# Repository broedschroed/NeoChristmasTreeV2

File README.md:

# NeoChristmasTree V2

An ESP32-powered Christmas tree ornament built from two interlocking,
fir-tree-shaped PCBs, lit by 66 individually addressable WS2812 LEDs and
controlled by an IR remote or a browser-based pattern editor.

## Highlights

- **66x WS2812 LEDs** across 4 wings (2 PCBs plugged together at a right
  angle, front and back of each), plus 2 tip LEDs at the very top.
- **IR remote control** — direct pattern selection, brightness, on/off, and
  a learnable sleep timer (30 minutes to 4 hours, set by repeatedly pressing
  the Timer button; the tree shows the corresponding "level" of its wings as
  live feedback).
- **Remote-learning mode** — any compatible IR remote's 13 buttons can be
  taught to the tree, with LED feedback on the tree itself during learning.
- **Browser-based pattern editor** — while powered via USB, the tree opens
  a local WiFi access point with a web UI (served from LittleFS) to create,
  edit, preview, and transfer lighting patterns between two trees.
- **Automatic brightness** — an onboard light sensor (LDR) adjusts LED
  brightness to the ambient light, capped by the brightness set via remote.
- **Proper power management** — on battery, switching off fully cuts power
  via a FET-driven double-click of the physical power button; on USB, the
  regulator stays active and only the LEDs go dark.

## Hardware

- ESP32 (NeoPixel data on pin 16)
- VS1838B IR receiver
- LDR for ambient-light sensing
- FET power switch to emulate a double-click power-off on battery
- Two interlocking fir-tree-shaped PCBs ("Tannenfluegellaengs" and
  "Tannenfluegelquer"), each carrying 32 of the 66 LEDs
- Main control board ("TannenbasisV4") carrying the ESP32, IR receiver, LDR
  and power management; KiCad sources for all three boards under
  `docs/Leiterplatten/`
- 3D-printed base housing; STL files under `docs/Gehäuse/`

## Repository layout

- `*.ino` / `*.h` — firmware (Arduino/ESP32 sketch)
- `data/www/` — the pattern editor web UI, uploaded to the ESP32's LittleFS
  filesystem (Arduino IDE "ESP32 Sketch Data Upload" or equivalent)
- `docs/manual/` — user manual (PDF)
- `docs/system/` — system documentation (PDF; describes an earlier hardware
  revision, kept for reference)
- `docs/Leiterplatten/` — KiCad sources, gerbers, schematic and front/back
  PCB renders for the control board and the two wing PCBs
- `docs/Gehäuse/` — STL files for the 3D-printed base housing
- `docs/Bilder/` — photos and a short clip of the finished tree

## Building

Open `NeoChristmasTreeV2.ino` in the Arduino IDE (or arduino-cli) with the
ESP32 core installed, plus the libraries IRremote, Adafruit NeoPixel,
ArduinoJson, and ESPAsyncWebServer. Flash the sketch, then upload the
contents of `data/` to the ESP32's LittleFS filesystem (e.g. via the "ESP32
Sketch Data Upload" tool) to make the pattern editor available.

Hold the mode/learn switch while powering on to enter IR remote-learning
mode.

## License

Released under the [MIT License](LICENSE).

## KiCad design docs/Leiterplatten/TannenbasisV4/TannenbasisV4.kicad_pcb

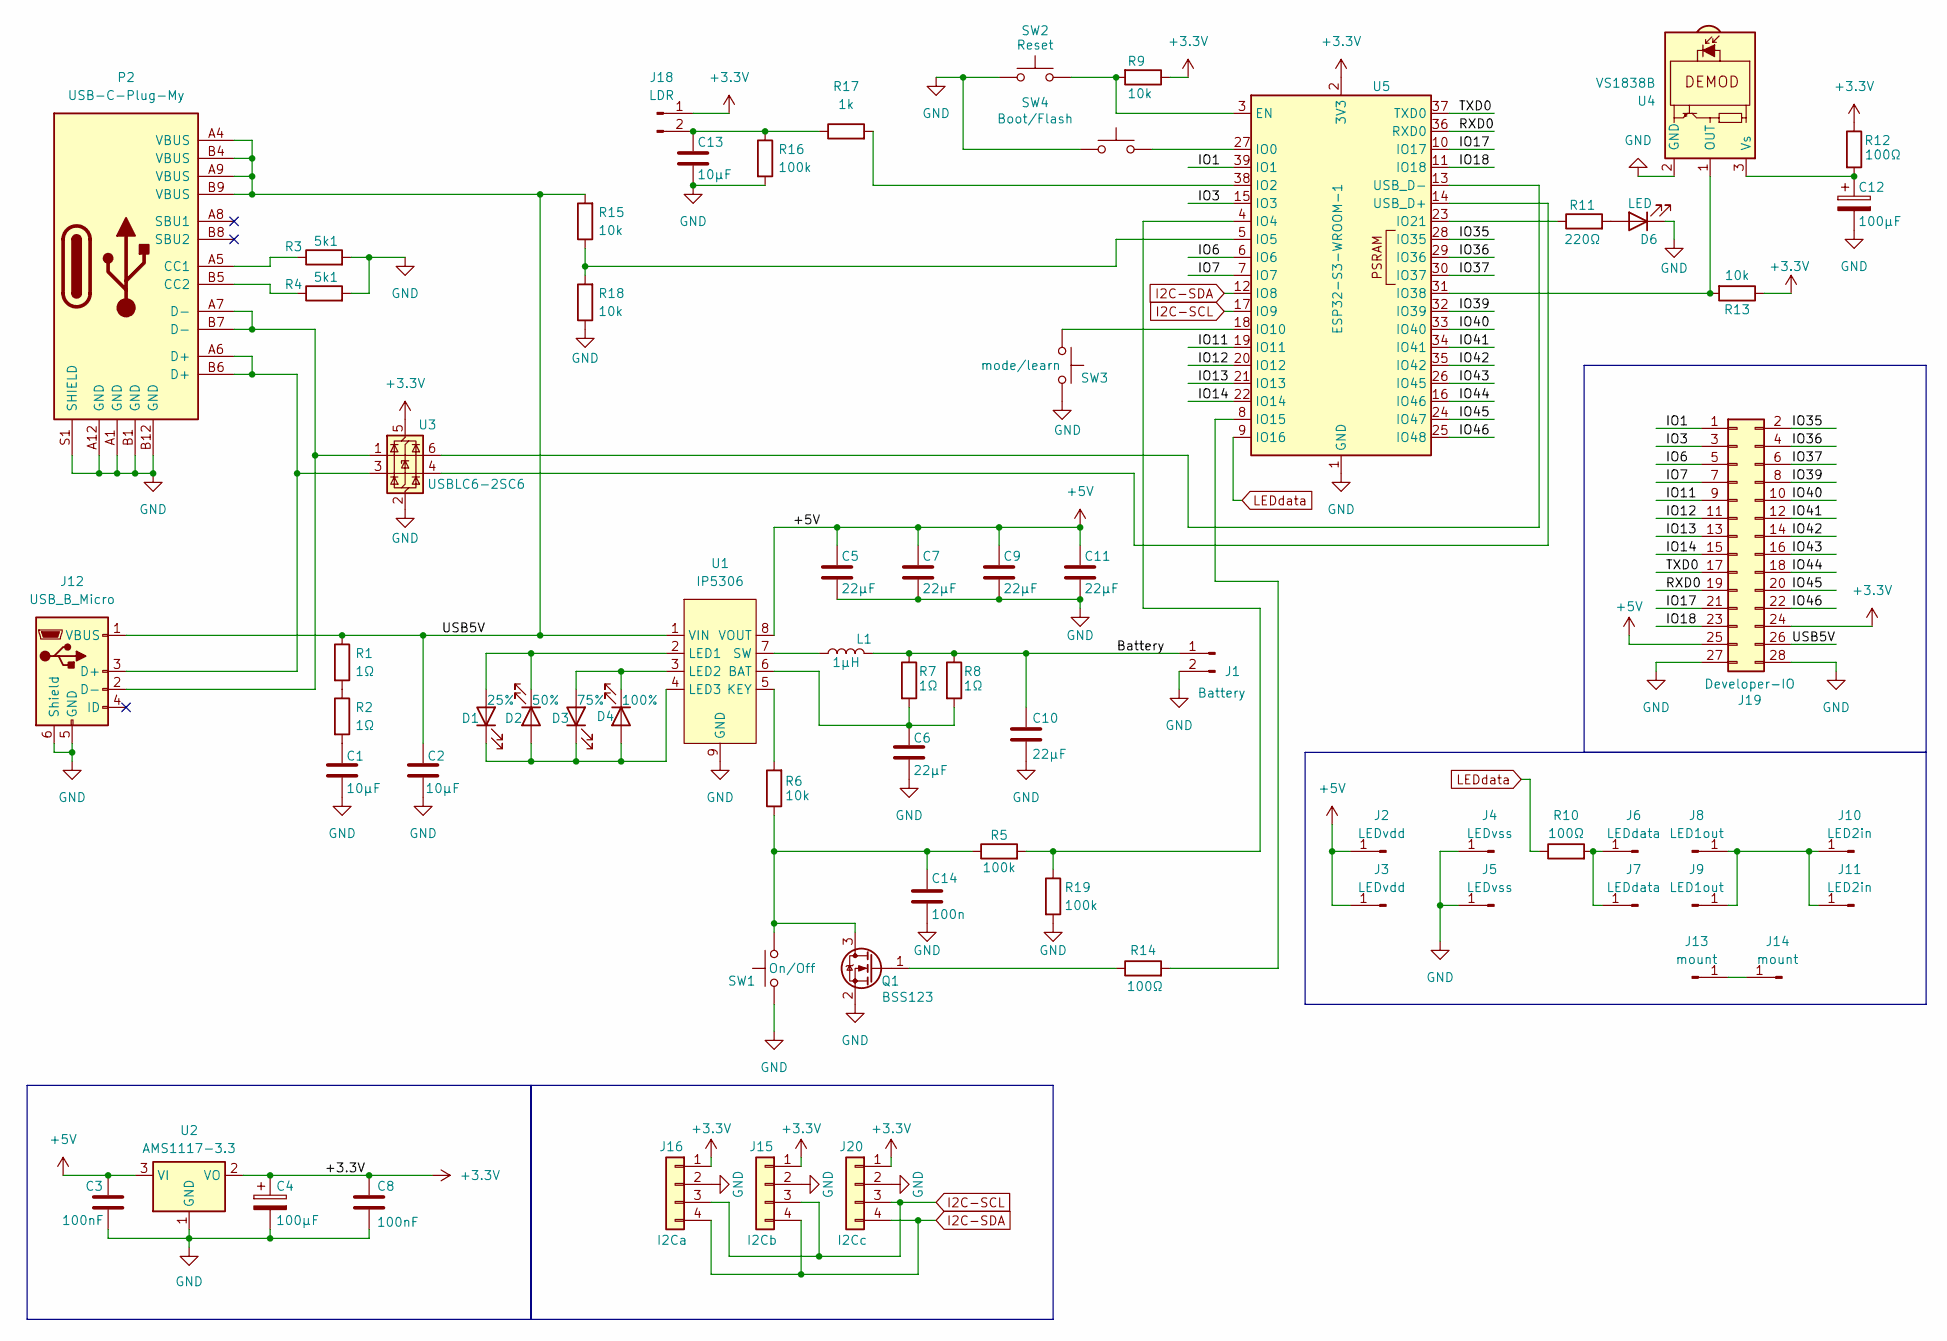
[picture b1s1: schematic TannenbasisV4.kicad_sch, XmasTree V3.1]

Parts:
C1, C2, C13: 10µF; C_0805_2012Metric_Pad1.18x1.45mm_HandSolder
C3, C8: 100nF; C_0805_2012Metric_Pad1.18x1.45mm_HandSolder
C4, C12: 100µF; CP_Radial_D6.3mm_P2.50mm
C5, C6, C7, C9, C10, C11: 22µF; C_1210_3225Metric_Pad1.33x2.70mm_HandSolder
C14: 100n; C_0805_2012Metric_Pad1.18x1.45mm_HandSolder
D1: 25%; LED_1210_3225Metric_Pad1.42x2.65mm_HandSolder
D2: 50%; LED_1210_3225Metric_Pad1.42x2.65mm_HandSolder
D3: 75%; LED_1210_3225Metric_Pad1.42x2.65mm_HandSolder
D4: 100%; LED_1210_3225Metric_Pad1.42x2.65mm_HandSolder
D6: LED; LED_1210_3225Metric_Pad1.42x2.65mm_HandSolder
J1: Battery; PinHeader_1x02_P2.54mm_Vertical
J2, J3: LEDvdd; solderconnect-1
J4, J5: LEDvss; solderconnect-1
J6, J7: LEDdata; solderconnect-1
J8, J9: LED1out; solderconnect-1
J10, J11: LED2in; solderconnect-1
J12: USB_B_Micro; USB_Micro-B_Pins
J13, J14: mount; solderconnect-1
J15: I2Cb; PinHeader_1x04_P2.54mm_Vertical
J16: I2Ca; PinHeader_1x04_P2.54mm_Vertical
J18: LDR; PinHeader_1x02_P2.54mm_Vertical
J19: Developer-IO; PinHeader_2x14_P2.54mm_Vertical
J20: I2Cc; PinHeader_1x04_P2.54mm_Vertical
L1: 1µH; MyPowerCoil
P2: USB-C-Plug-My; MyUSB-C
Q1: BSS123; SOT-23
R1, R2, R7, R8: 1Ω; R_0805_2012Metric_Pad1.20x1.40mm_HandSolder
R3, R4: 5k1; R_0805_2012Metric_Pad1.20x1.40mm_HandSolder
R5, R16, R19: 100k; R_0805_2012Metric_Pad1.20x1.40mm_HandSolder
R6, R9, R13, R15, R18: 10k; R_0805_2012Metric_Pad1.20x1.40mm_HandSolder
R10, R12, R14: 100Ω; R_0805_2012Metric_Pad1.20x1.40mm_HandSolder
R11: 220Ω; R_0805_2012Metric_Pad1.20x1.40mm_HandSolder
R17: 1k; R_0805_2012Metric_Pad1.20x1.40mm_HandSolder
SW1: On/Off; SW_DIP_SPSTx01_Slide_6.7x4.1mm_W8.61mm_P2.54mm_LowProfile
SW2: Reset; SW_DIP_SPSTx01_Slide_6.7x4.1mm_W8.61mm_P2.54mm_LowProfile
SW3: mode/learn; SW_DIP_SPSTx01_Slide_6.7x4.1mm_W8.61mm_P2.54mm_LowProfile
SW4: Boot/Flash; SW_DIP_SPSTx01_Slide_6.7x4.1mm_W8.61mm_P2.54mm_LowProfile
U1: IP5306
U2: AMS1117-3.3; SOT-223-3_TabPin2
U3: USBLC6-2SC6; SOT-23-6
U4: VS1838B; Vishay_MOLD-3Pin
U5: ESP32-S3-WROOM-1

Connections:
+3.3V: C4.1, C8.1, J15.1, J16.1, J18.1, J19.24, J20.1, R9.1, R12.1, R13.1, U2.2 (VO), U3.5 (VBUS), U5.2 (3V3)
+5V: C3.1, C5.1, C7.1, C9.1, C11.1, J2.1, J3.1, J19.25, U1.8 (VOUT), U2.3 (VI)
/Battery: C10.1, J1.1, L1.2, R7.1, R8.1
/IO1: J19.1, U5.39 (IO1)
/IO3: J19.3, U5.15 (IO3)
/IO6: J19.5, U5.6 (IO6)
/IO7: J19.7, U5.7 (IO7)
/IO11: J19.9, U5.19 (IO11)
/IO12: J19.11, U5.20 (IO12)
/IO13: J19.13, U5.21 (IO13)
/IO14: J19.15, U5.22 (IO14)
/IO17: J19.21, U5.10 (IO17)
/IO18: J19.23, U5.11 (IO18)
/IO35: J19.2, U5.28 (IO35)
/IO36: J19.4, U5.29 (IO36)
/IO37: J19.6, U5.30 (IO37)
/IO39: J19.8, U5.32 (IO39)
/IO40: J19.10, U5.33 (IO40)
/IO41: J19.12, U5.34 (IO41)
/IO42: J19.14, U5.35 (IO42)
/IO43: J19.16, U5.26 (IO45)
/IO44: J19.18, U5.16 (IO46)
/IO45: J19.20, U5.24 (IO47)
/IO46: J19.22, U5.25 (IO48)
/RXD0: J19.19, U5.36 (RXD0)
/TXD0: J19.17, U5.37 (TXD0)
/USB5V: C2.1, J12.1 (VBUS), J19.26, P2.A4 (VBUS), P2.A9 (VBUS), P2.B4 (VBUS), P2.B9 (VBUS), R1.1, R15.2, U1.1 (VIN)
GND: C1.2, C2.2, C3.2, C4.2, C5.2, C6.2, C7.2, C8.2, C9.2, C10.2, C11.2, C12.2, C13.2, C14.2, D6.1 (K), J1.2, J4.1, J5.1, J12.5 (GND), J12.6 (Shield), J15.2, J16.2, J19.27, J19.28, J20.2, P2.A1 (GND), P2.A12 (GND), P2.B1 (GND), P2.B12 (GND), P2.S1 (SHIELD), Q1.2 (S), R3.2, R4.2, R16.2, R18.1, R19.2, SW1.1, SW2.1, SW3.2, SW4.2, U1.9 (GND), U2.1 (GND), U3.2 (GND), U4.2 (GND), U5.1 (GND), U5.40 (GND), U5.41 (GND)
I2C-SCL: J15.3, J16.3, J20.3, U5.17 (IO9)
I2C-SDA: J15.4, J16.4, J20.4, U5.12 (IO8)
LEDdata: R10.1, U5.9 (IO16)
unnamed: C1.1, R2.2
unnamed: D1.2 (A), D2.1 (K), U1.2 (LED1)
unnamed: D1.1 (K), D2.2 (A), D3.1 (K), D4.2 (A), U1.4 (LED3)
unnamed: D3.2 (A), D4.1 (K), U1.3 (LED2)
unnamed: D6.2 (A), R11.2
unnamed: J6.1, J7.1, R10.2
unnamed: J8.1, J9.1, J10.1, J11.1
unnamed: J12.3 (D+), P2.A6 (D+), P2.B6 (D+), U3.3 (I/O2)
unnamed: J12.2 (D-), P2.A7 (D-), P2.B7 (D-), U3.1 (I/O1)
unnamed: J13.1, J14.1
unnamed: C13.1, J18.2, R16.1, R17.1
unnamed: P2.A5 (CC1), R3.1
unnamed: P2.B5 (CC2), R4.1
unnamed: C14.1, Q1.3 (D), R5.1, R6.1, SW1.2
unnamed: Q1.1 (G), R14.1
unnamed: R1.2, R2.1
unnamed: C6.1, R7.2, R8.2, U1.6 (BAT)
unnamed: R6.2, U1.5 (KEY)
unnamed: L1.1, U1.7 (SW)
unnamed: R13.2, U4.1 (OUT), U5.31 (IO38)
unnamed: C12.1, R12.2, U4.3 (Vs)
unnamed: R9.2, SW2.2, U5.3 (EN)
unnamed: SW4.1, U5.27 (IO0)
unnamed: R17.2, U5.38 (IO2)
unnamed: R5.2, R19.1, U5.4 (IO4)
unnamed: R15.1, R18.2, U5.5 (IO5)
unnamed: SW3.1, U5.18 (IO10)
unnamed: R14.2, U5.8 (IO15)
unnamed: R11.1, U5.23 (IO21)
unnamed: U3.4 (I/O2), U5.14 (USB_D+)
unnamed: U3.6 (I/O1), U5.13 (USB_D-)

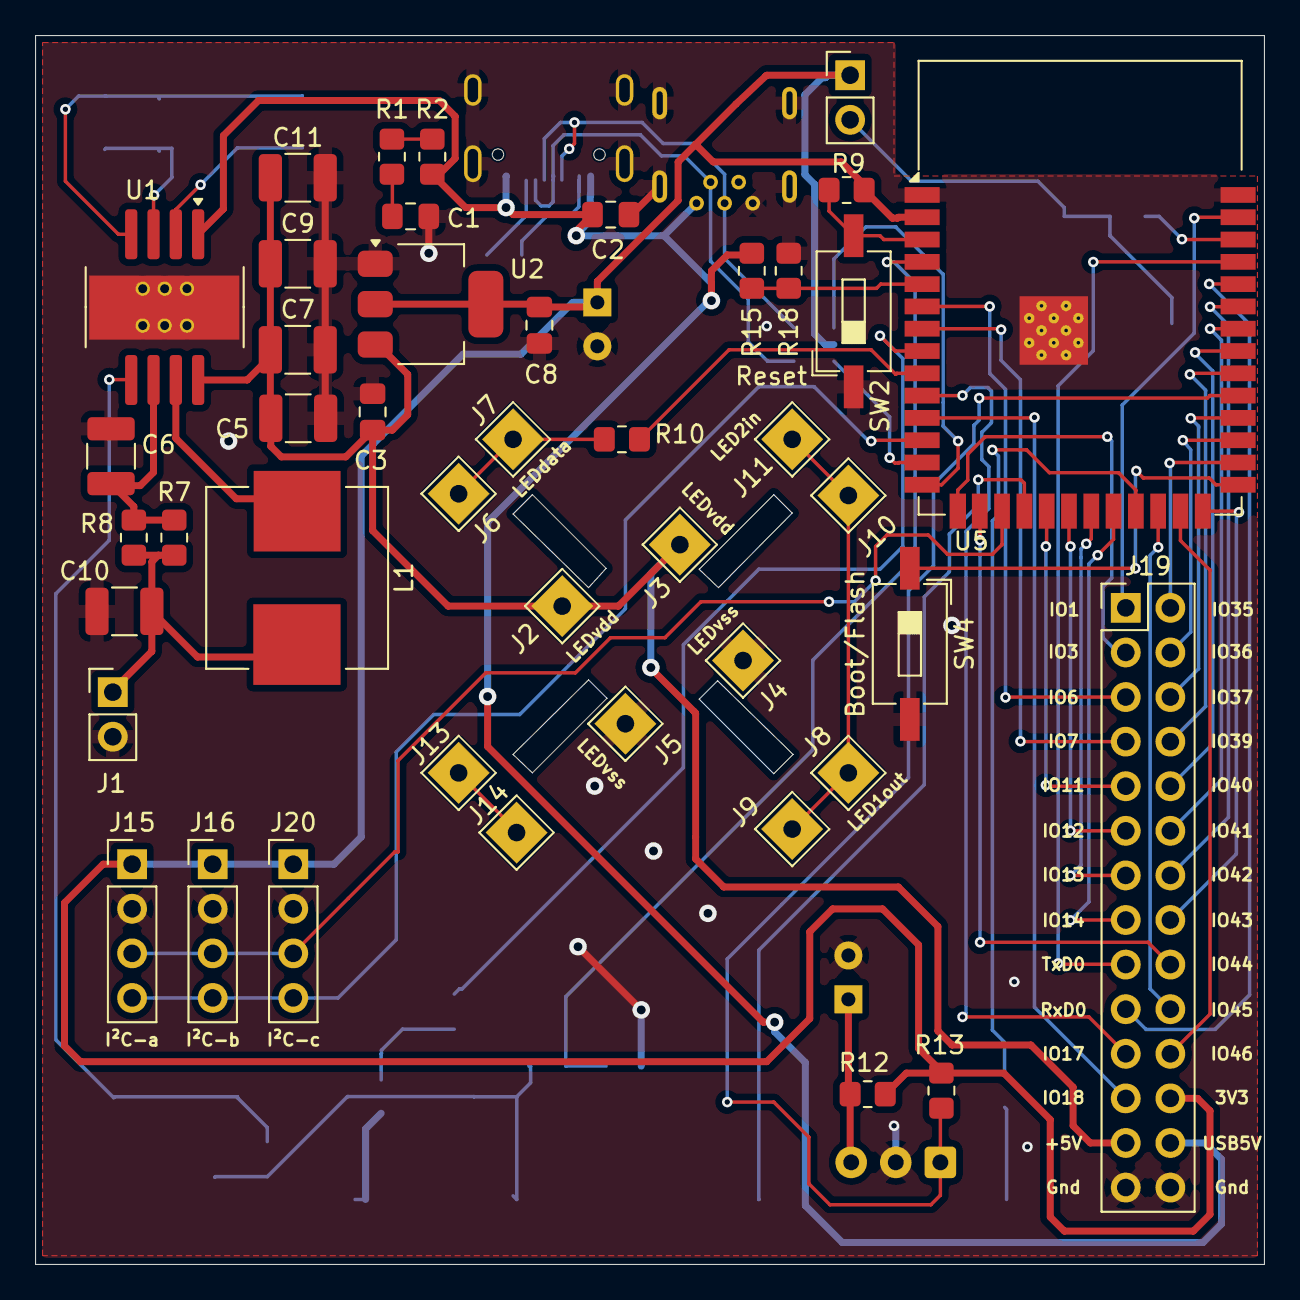
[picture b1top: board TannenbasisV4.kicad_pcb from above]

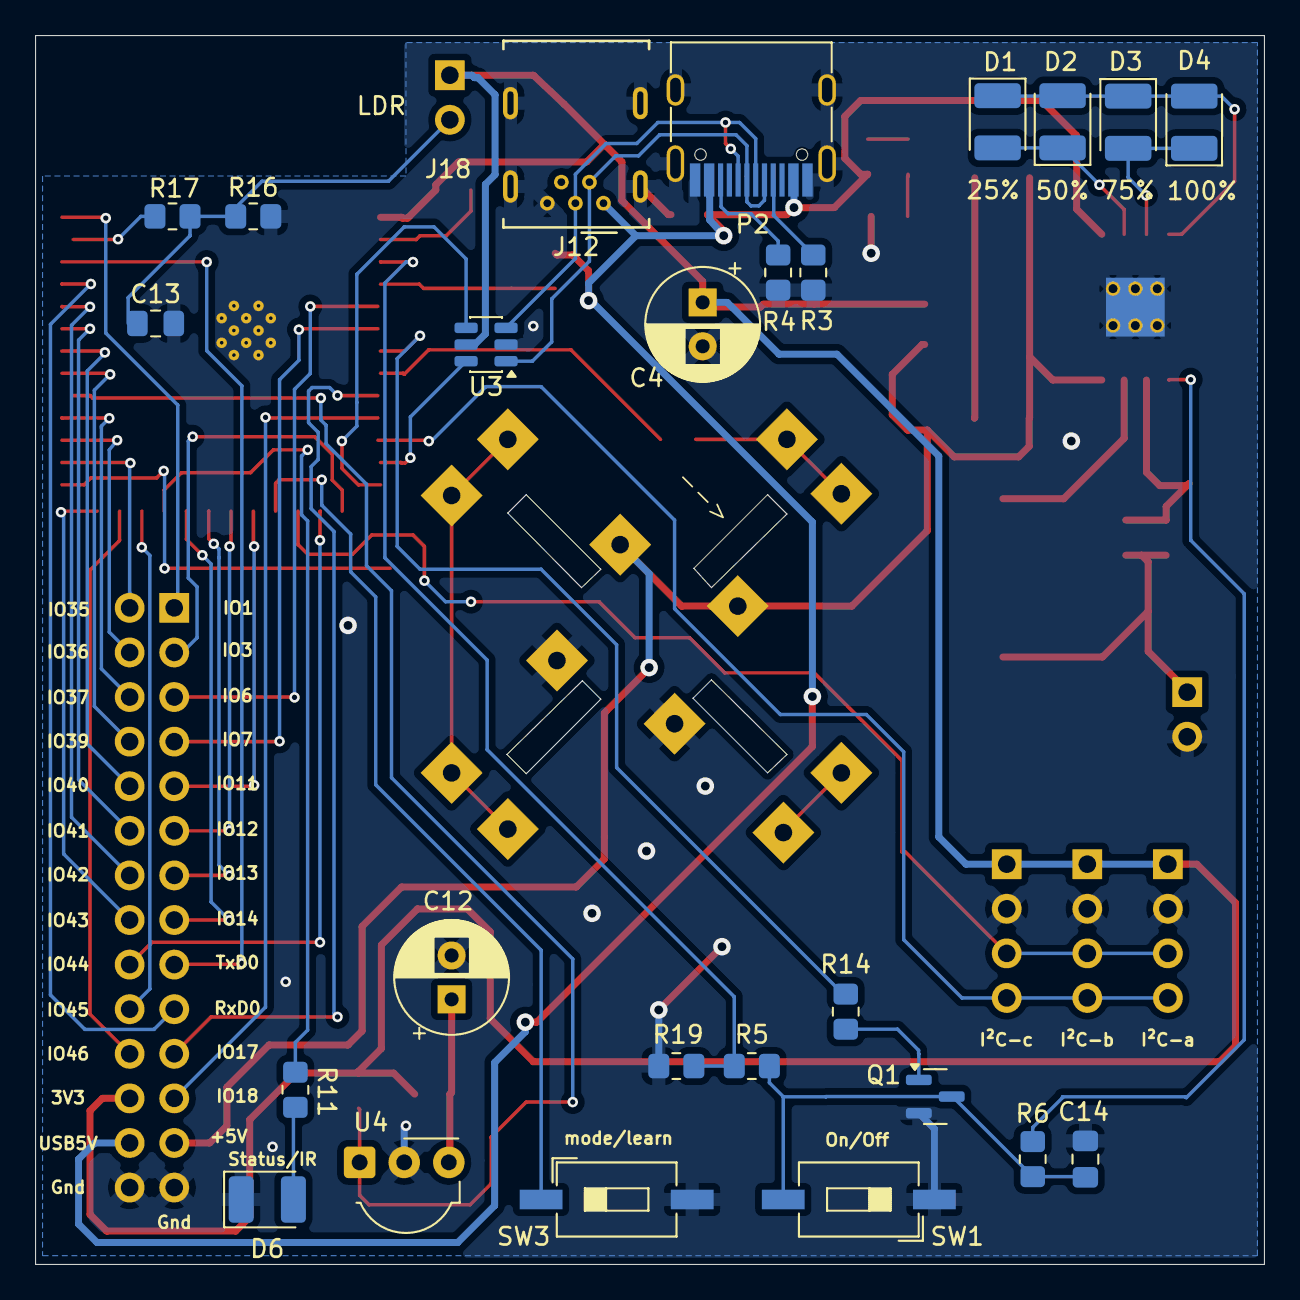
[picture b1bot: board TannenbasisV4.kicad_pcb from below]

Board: 2 copper layers, 70.0 x 70.0 mm, 69 parts (25 on the bottom side), 62 nets.

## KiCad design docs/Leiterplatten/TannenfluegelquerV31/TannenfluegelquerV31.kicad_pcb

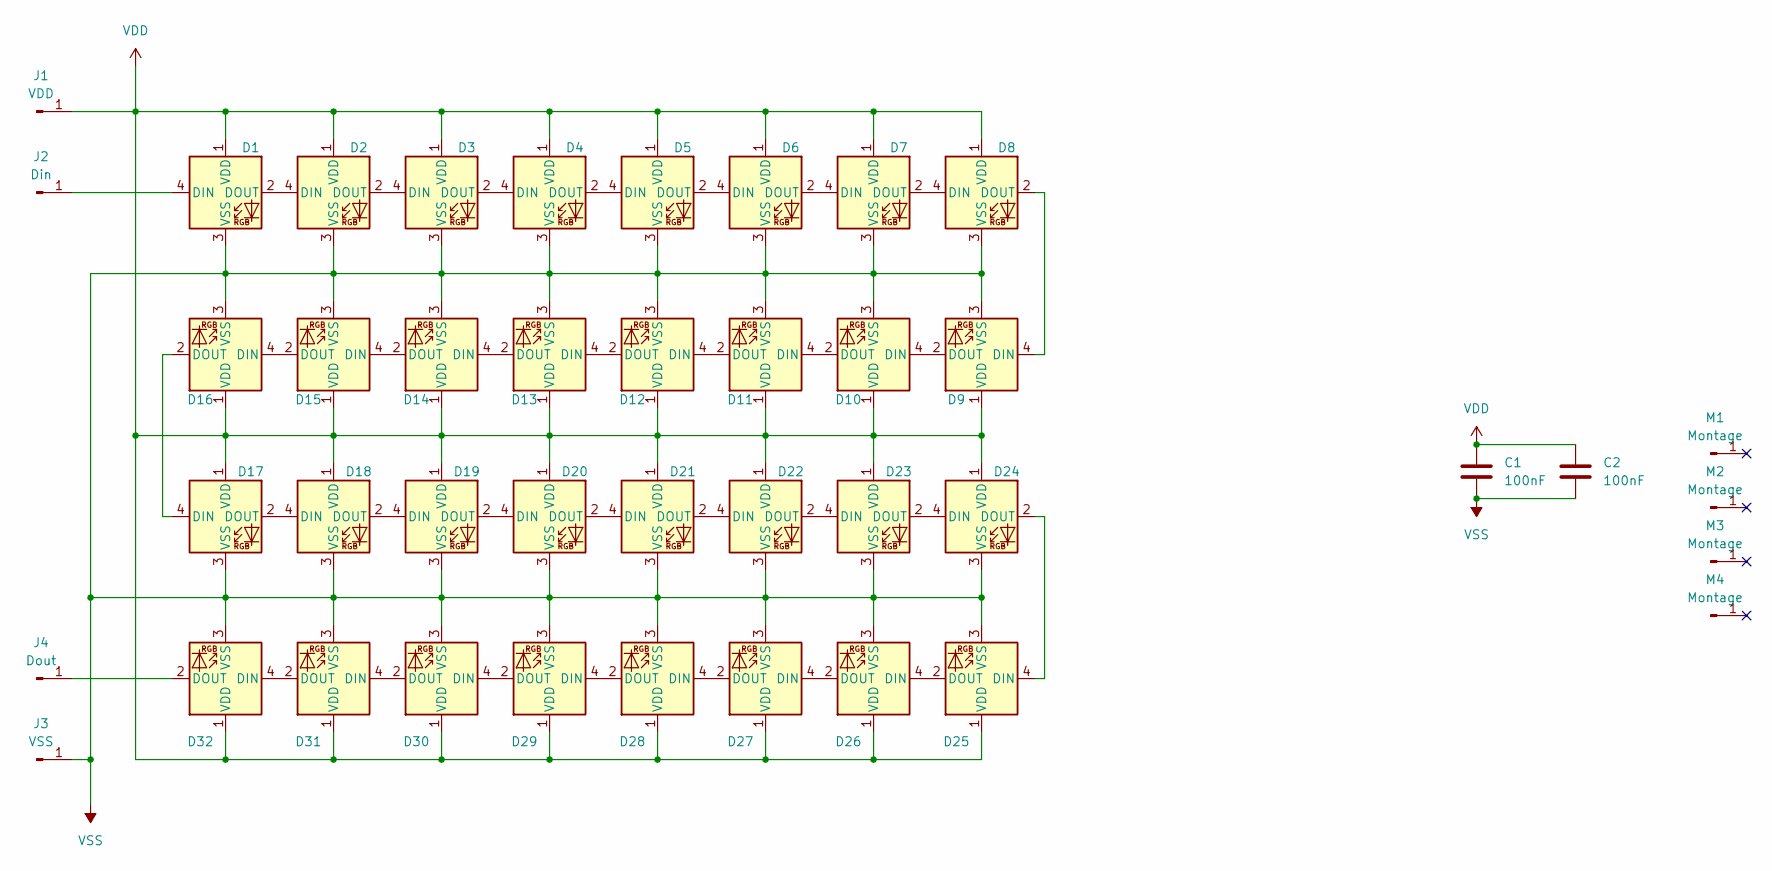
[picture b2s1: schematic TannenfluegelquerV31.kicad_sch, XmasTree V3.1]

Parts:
C1, C2: 100nF; C_0805_2012Metric_Pad1.18x1.45mm_HandSolder
D1, D2, D3, D4, D5, D6, D7, D8, D9, D10, D11, D12, D13, D14, D15, D16, D17, D18, D19, D20, D21, D22, D23, D24, D25, D26, D27, D28, D29, D30, D31, D32: WS2812B; LED_WS2812B_PLCC4_5.0x5.0mm_P3.2mm
J1: VDD; solderconnect-1
J2: Din; solderconnect-1
J3: VSS; solderconnect-1
J4: Dout; solderconnect-1
M1, M2, M3, M4: Montage; solderconnect-1

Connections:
unnamed: D1.4 (DIN), J2.1
unnamed: D1.2 (DOUT), D2.4 (DIN)
unnamed: D2.2 (DOUT), D3.4 (DIN)
unnamed: D3.2 (DOUT), D4.4 (DIN)
unnamed: D4.2 (DOUT), D5.4 (DIN)
unnamed: D5.2 (DOUT), D6.4 (DIN)
unnamed: D6.2 (DOUT), D7.4 (DIN)
unnamed: D7.2 (DOUT), D8.4 (DIN)
unnamed: D8.2 (DOUT), D9.4 (DIN)
unnamed: D9.2 (DOUT), D10.4 (DIN)
unnamed: D10.2 (DOUT), D11.4 (DIN)
unnamed: D11.2 (DOUT), D12.4 (DIN)
unnamed: D12.2 (DOUT), D13.4 (DIN)
unnamed: D13.2 (DOUT), D14.4 (DIN)
unnamed: D14.2 (DOUT), D15.4 (DIN)
unnamed: D15.2 (DOUT), D16.4 (DIN)
unnamed: D16.2 (DOUT), D17.4 (DIN)
unnamed: D17.2 (DOUT), D18.4 (DIN)
unnamed: D18.2 (DOUT), D19.4 (DIN)
unnamed: D19.2 (DOUT), D20.4 (DIN)
unnamed: D20.2 (DOUT), D21.4 (DIN)
unnamed: D21.2 (DOUT), D22.4 (DIN)
unnamed: D22.2 (DOUT), D23.4 (DIN)
unnamed: D23.2 (DOUT), D24.4 (DIN)
unnamed: D24.2 (DOUT), D25.4 (DIN)
unnamed: D25.2 (DOUT), D26.4 (DIN)
unnamed: D26.2 (DOUT), D27.4 (DIN)
unnamed: D27.2 (DOUT), D28.4 (DIN)
unnamed: D28.2 (DOUT), D29.4 (DIN)
unnamed: D29.2 (DOUT), D30.4 (DIN)
unnamed: D30.2 (DOUT), D31.4 (DIN)
unnamed: D31.2 (DOUT), D32.4 (DIN)
unnamed: D32.2 (DOUT), J4.1
VDD: C1.1, C2.1, D1.1 (VDD), D2.1 (VDD), D3.1 (VDD), D4.1 (VDD), D5.1 (VDD), D6.1 (VDD), D7.1 (VDD), D8.1 (VDD), D9.1 (VDD), D10.1 (VDD), D11.1 (VDD), D12.1 (VDD), D13.1 (VDD), D14.1 (VDD), D15.1 (VDD), D16.1 (VDD), D17.1 (VDD), D18.1 (VDD), D19.1 (VDD), D20.1 (VDD), D21.1 (VDD), D22.1 (VDD), D23.1 (VDD), D24.1 (VDD), D25.1 (VDD), D26.1 (VDD), D27.1 (VDD), D28.1 (VDD), D29.1 (VDD), D30.1 (VDD), D31.1 (VDD), D32.1 (VDD), J1.1
VSS: C1.2, C2.2, D1.3 (VSS), D2.3 (VSS), D3.3 (VSS), D4.3 (VSS), D5.3 (VSS), D6.3 (VSS), D7.3 (VSS), D8.3 (VSS), D9.3 (VSS), D10.3 (VSS), D11.3 (VSS), D12.3 (VSS), D13.3 (VSS), D14.3 (VSS), D15.3 (VSS), D16.3 (VSS), D17.3 (VSS), D18.3 (VSS), D19.3 (VSS), D20.3 (VSS), D21.3 (VSS), D22.3 (VSS), D23.3 (VSS), D24.3 (VSS), D25.3 (VSS), D26.3 (VSS), D27.3 (VSS), D28.3 (VSS), D29.3 (VSS), D30.3 (VSS), D31.3 (VSS), D32.3 (VSS), J3.1

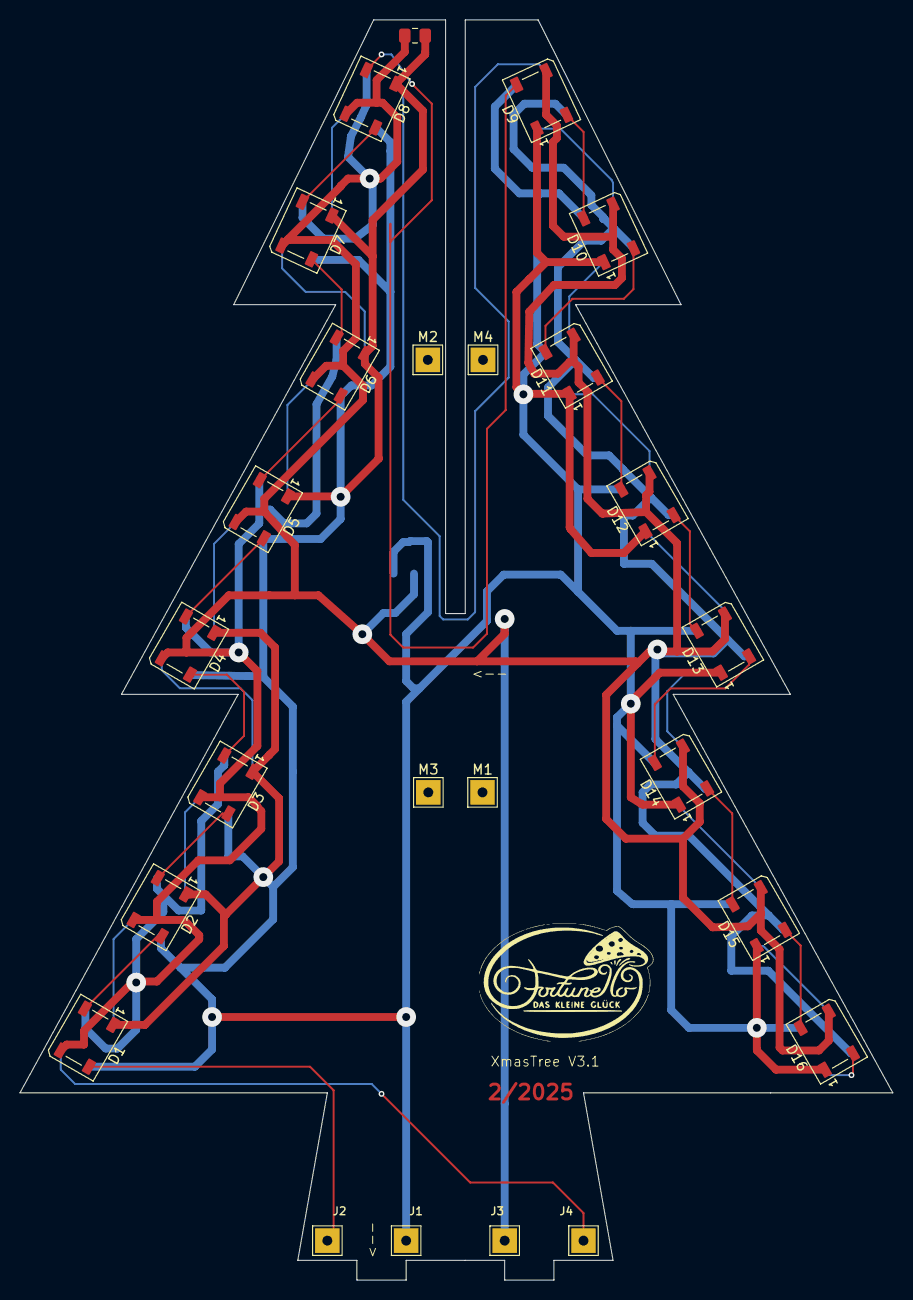
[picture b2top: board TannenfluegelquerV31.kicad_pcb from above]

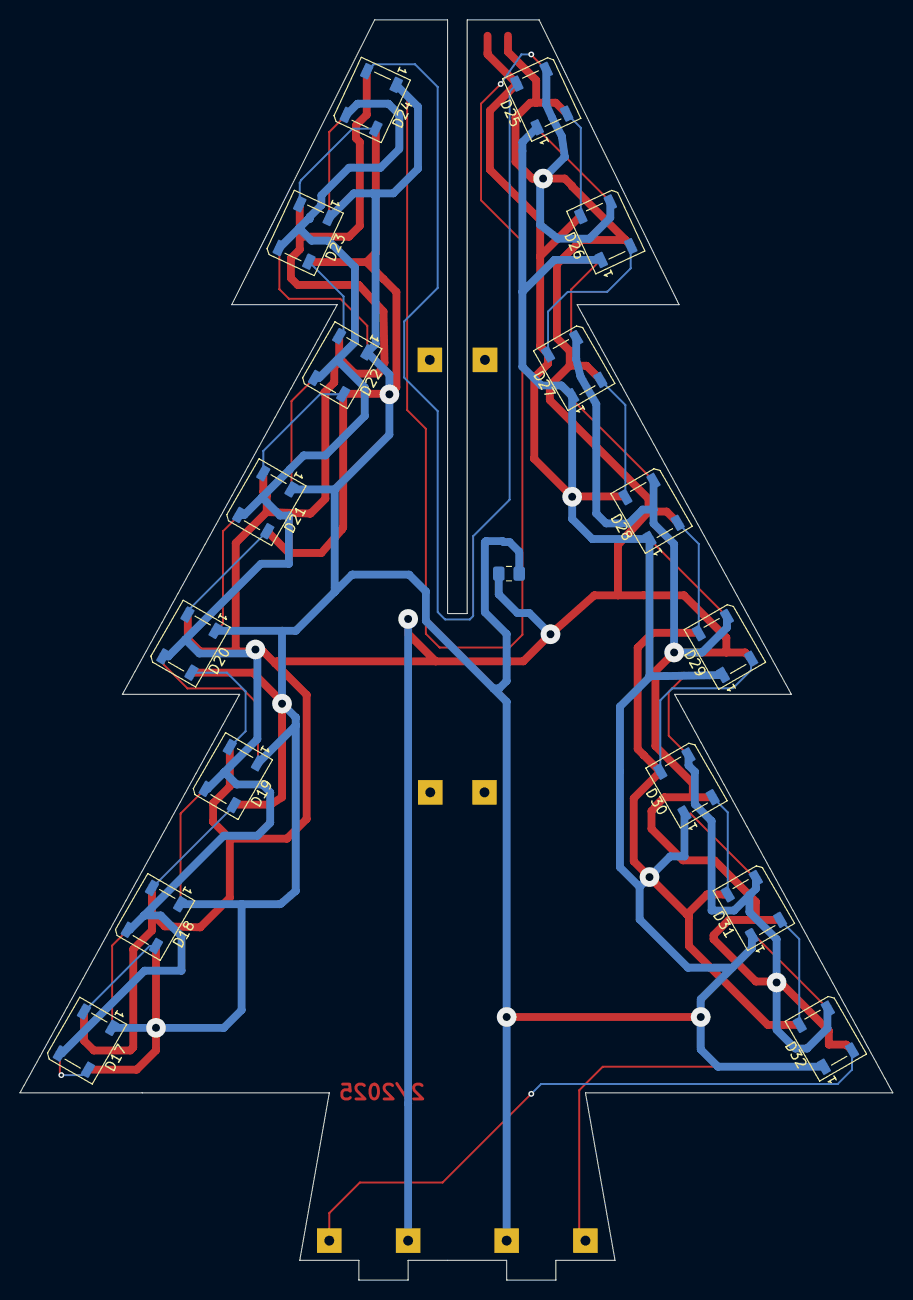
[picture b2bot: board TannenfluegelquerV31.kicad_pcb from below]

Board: 2 copper layers, 88.6 x 127.9 mm, 42 parts (17 on the bottom side), 35 nets.
